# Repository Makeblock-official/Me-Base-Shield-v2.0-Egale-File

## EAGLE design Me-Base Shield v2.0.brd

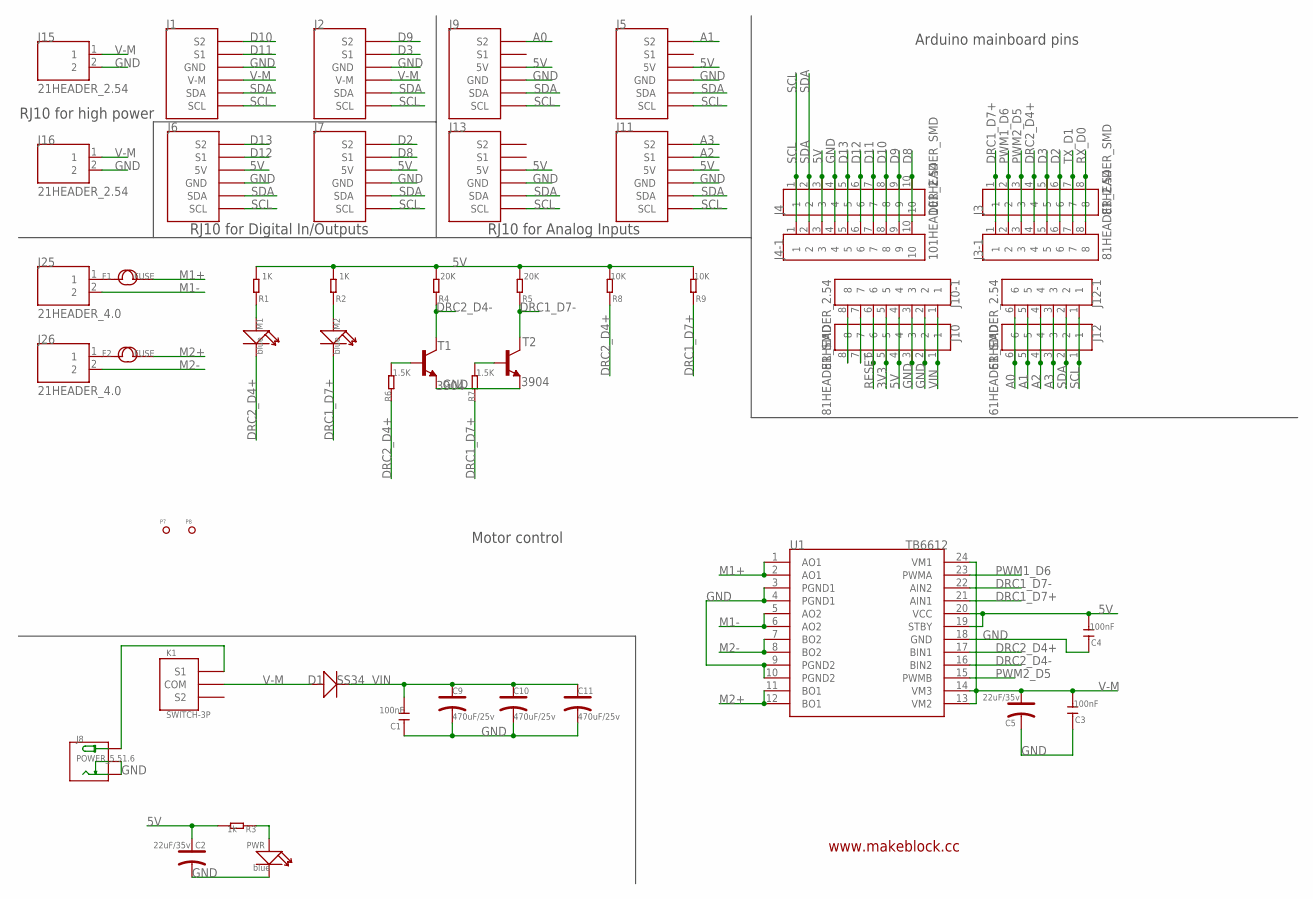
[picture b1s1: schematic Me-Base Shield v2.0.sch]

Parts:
C1, C3, C4: 100nF; 0603
C2, C5: 22uF/35v; ELECTRO-SMD-B-4.8MM
C9, C10, C11: 470uF/25v; ELECTRO-SMD-E-7.8MM
D1: SS34; D2010
F1, F2: FUSE
J1, J2: RJ11-6P6C-MOTOR; RJ11-6P6C
J3, J10: 81HEADER_SMD; 8*1HEADER_SMD
J3-1, J10-1: 81HEADER_2.54; 8*1HEADER_2.54
J4: 101HEADER_SMD; 10*1HEADER_SMD
J4-1: 101HEADER_2.54; 10*1HEADER_2.54
J5, J6, J7, J9, J11, J13: RJ11-6P6C-DIGI; RJ11-6P6C
J8: POWER_5.51.6; POWER_5.5*1.6
J12: 61HEADER_SMD; 6*1HEADER_SMD
J12-1: 61HEADER_2.54; 6*1HEADER_2.54
J15, J16: 21HEADER_2.54; 2*1HEADER_2.54
J25, J26: 21HEADER_4.0; 2*1HEADER_4.0
K1: SWITCH-3P; SWITCH_3P
M1, M2: blue; LED-0603
P7, P8: PAD-MARK; ROUND-MARK-1.0
PWR: blue; LED-0603
R1, R2: 1K; 0603
R3: 1k; 0603
R4, R5: 20K; 0603
R6, R7: 1.5K; 0603
R8, R9: 10K; 0603
T1, T2: 3904
U1: TB6612; TB6612FNG

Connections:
3V3: J10.5, J10-1.5
5V: C2.+, C4.2, J4.3, J4-1.3, J5.4 (5V), J6.4 (5V), J7.4 (5V), J9.4 (5V), J10.4, J10-1.4, J11.4 (5V), J13.4 (5V), R1.2, R2.2, R3.2, R4.2, R5.2, R8.2, R9.2, U1.19 (STBY), U1.20 (VCC)
A0: J9.6 (S2), J12.6, J12-1.6
A1: J5.6 (S2), J12.5, J12-1.5
A2: J11.5 (S1), J12.4, J12-1.4
A3: J11.6 (S2), J12.3, J12-1.3
D2: J3.6, J3-1.6, J7.6 (S2)
D3: J2.5 (S1), J3.5, J3-1.5
D8: J4.10, J4-1.10, J7.5 (S1)
D9: J2.6 (S2), J4.9, J4-1.9
D10: J1.6 (S2), J4.8, J4-1.8
D11: J1.5 (S1), J4.7, J4-1.7
D12: J4.6, J4-1.6, J6.5 (S1)
D13: J4.5, J4-1.5, J6.6 (S2)
DRC1_D7+: J3.1, J3-1.1, M2.-, R7.1, R9.1, U1.21 (AIN1)
DRC1_D7-: R5.1, T2.3 (C), U1.22 (AIN2)
DRC2_D4+: J3.4, J3-1.4, M1.-, R6.1, R8.1, U1.17 (BIN1)
DRC2_D4-: R4.1, T1.3 (C), U1.16 (BIN2)
GND: C1.1, C2.-, C3.1, C4.1, C5.-, C9.-, C10.-, C11.-, J1.4 (GND), J2.4 (GND), J4.4, J4-1.4, J5.3 (GND), J6.3 (GND), J7.3 (GND), J8.1 (-), J8.2 (-), J8.3 (-), J8.4 (-), J8.5 (-), J8.6 (-), J8.7 (-), J8.8 (-), J8.9 (-), J8.10 (-), J8.11 (-), J8.12 (-), J8.13 (CDN), J8.14 (CDN), J8.15 (CDN), J8.16 (CDN), J8.17 (CDN), J8.18 (CDN), J8.19 (CDN), J8.20 (CDN), J8.21 (CDN), J8.22 (CDN), J8.23 (CDN), J8.24 (CDN), J8.-, J8.CDN, J9.3 (GND), J10.2, J10.3, J10-1.2, J10-1.3, J11.3 (GND), J13.3 (GND), J15.2, J16.2, PWR.-, T1.2 (E), T2.2 (E), U1.3 (PGND1), U1.4 (PGND1), U1.9 (PGND2), U1.10 (PGND2), U1.18 (GND)
M1+: F1.2, U1.1 (AO1), U1.2 (AO1)
M1-: J25.2, U1.5 (AO2), U1.6 (AO2)
M2+: F2.2, U1.11 (BO1), U1.12 (BO1)
M2-: J26.2, U1.7 (BO2), U1.8 (BO2)
unnamed: J10.7, J10-1.7
unnamed: J10.8, J10-1.8
unnamed: M1.+, R1.1
unnamed: M2.+, R2.1
unnamed: PWR.+, R3.1
unnamed: F1.1, J25.1
unnamed: J8.25 (+), J8.26 (+), J8.27 (+), J8.28 (+), J8.29 (+), J8.30 (+), J8.31 (+), J8.32 (+), J8.33 (+), J8.34 (+), J8.35 (+), J8.36 (+), J8.+, K1.1 (S1), K1.P$6 (S1), K1.P$16 (S1), K1.P$17 (S1), K1.P$18 (S1), K1.P$20 (S1), K1.P$21 (S1)
unnamed: F2.1, J26.1
unnamed: R6.2, T1.1 (B)
unnamed: R7.2, T2.1 (B)
PWM1_D6: J3.2, J3-1.2, U1.23 (PWMA)
PWM2_D5: J3.3, J3-1.3, U1.15 (PWMB)
RESET: J10.6, J10-1.6
RX_D0: J3.8, J3-1.8
SCL: J1.1 (SCL), J2.1 (SCL), J4.1, J4-1.1, J5.1 (SCL), J6.1 (SCL), J7.1 (SCL), J9.1 (SCL), J11.1 (SCL), J12.1, J12-1.1, J13.1 (SCL)
SDA: J1.2 (SDA), J2.2 (SDA), J4.2, J4-1.2, J5.2 (SDA), J6.2 (SDA), J7.2 (SDA), J9.2 (SDA), J11.2 (SDA), J12.2, J12-1.2, J13.2 (SDA)
TX_D1: J3.7, J3-1.7
V-M: C3.2, C5.+, D1.+, J1.3 (V-M), J2.3 (V-M), J15.1, J16.1, K1.2 (COM), K1.P$1 (COM), K1.P$2 (COM), K1.P$3 (COM), K1.P$4 (COM), K1.P$5 (COM), K1.P$7 (COM), U1.13 (VM2), U1.14 (VM3), U1.24 (VM1)
VIN: C1.2, C9.+, C10.+, C11.+, D1.-, J10.1, J10-1.1

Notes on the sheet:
RJ10 for Analog Inputs
RJ10 for high power
RJ10 for Digital In/Outputs
Arduino mainboard pins
Motor control
www.makeblock.cc

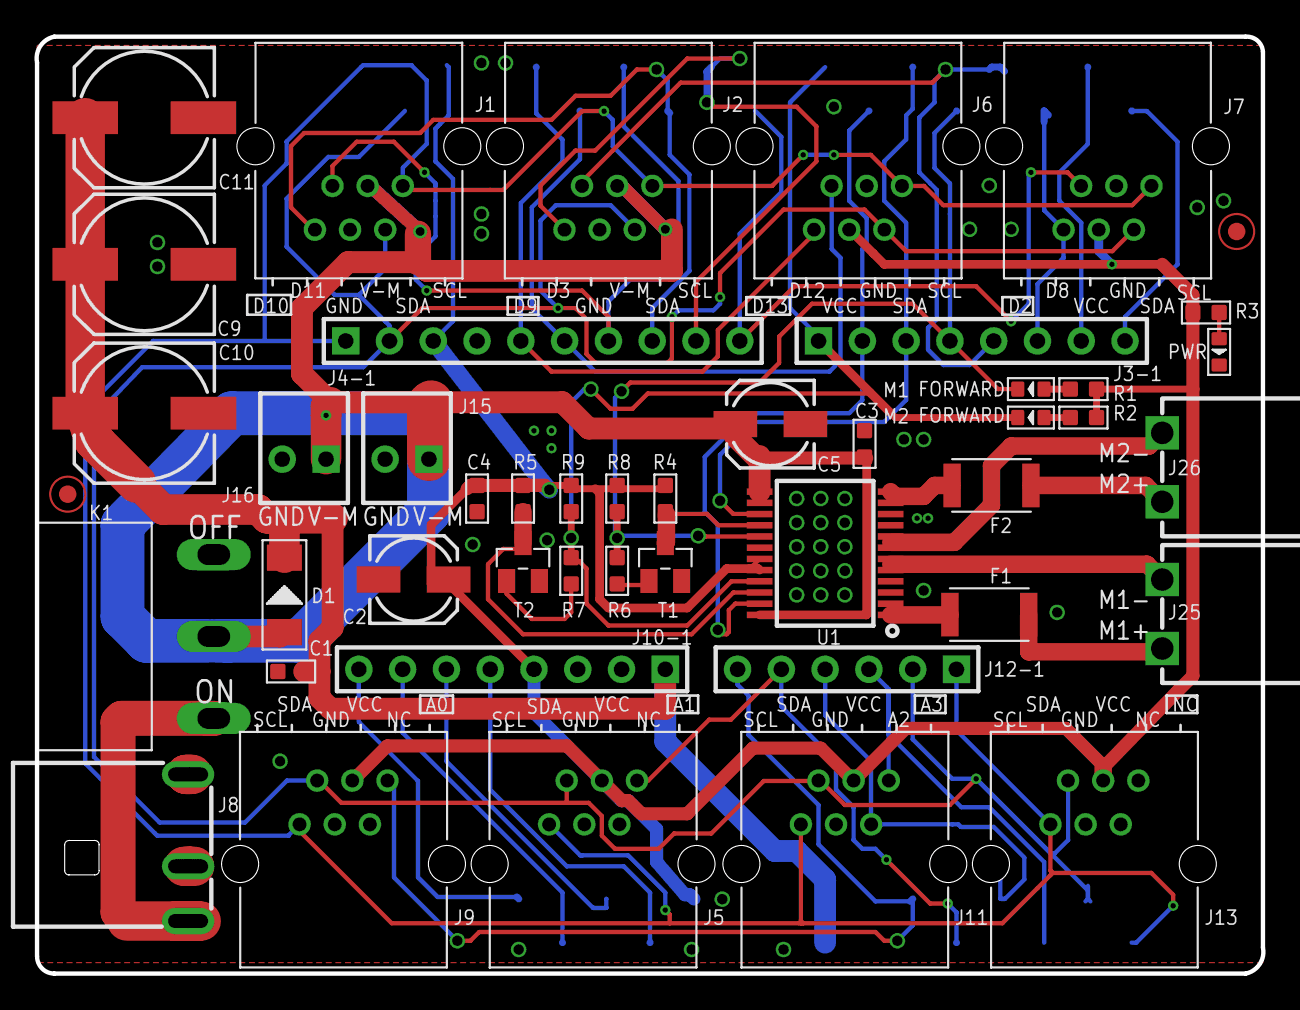
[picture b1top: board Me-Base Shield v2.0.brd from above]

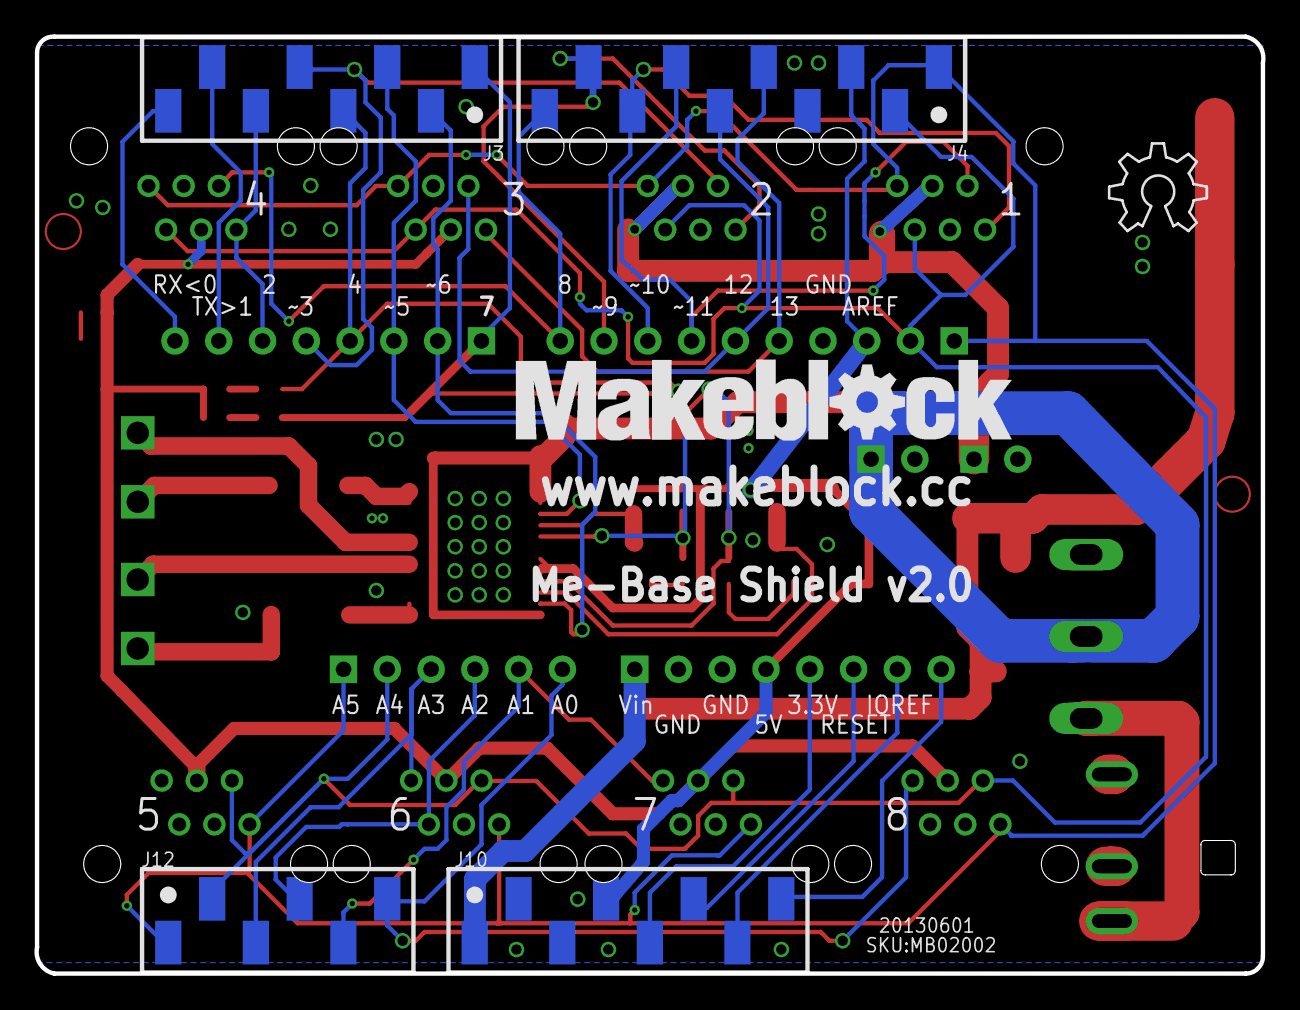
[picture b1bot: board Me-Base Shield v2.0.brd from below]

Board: 2 copper layers, 71.2 x 54.4 mm, 51 parts (5 on the bottom side), 42 nets.

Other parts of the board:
U$2: OSHW_6X200_NOTEXT

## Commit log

2013-08-27 PCB files
2013-08-27 Me-Base Shield v2.0 Shematic
